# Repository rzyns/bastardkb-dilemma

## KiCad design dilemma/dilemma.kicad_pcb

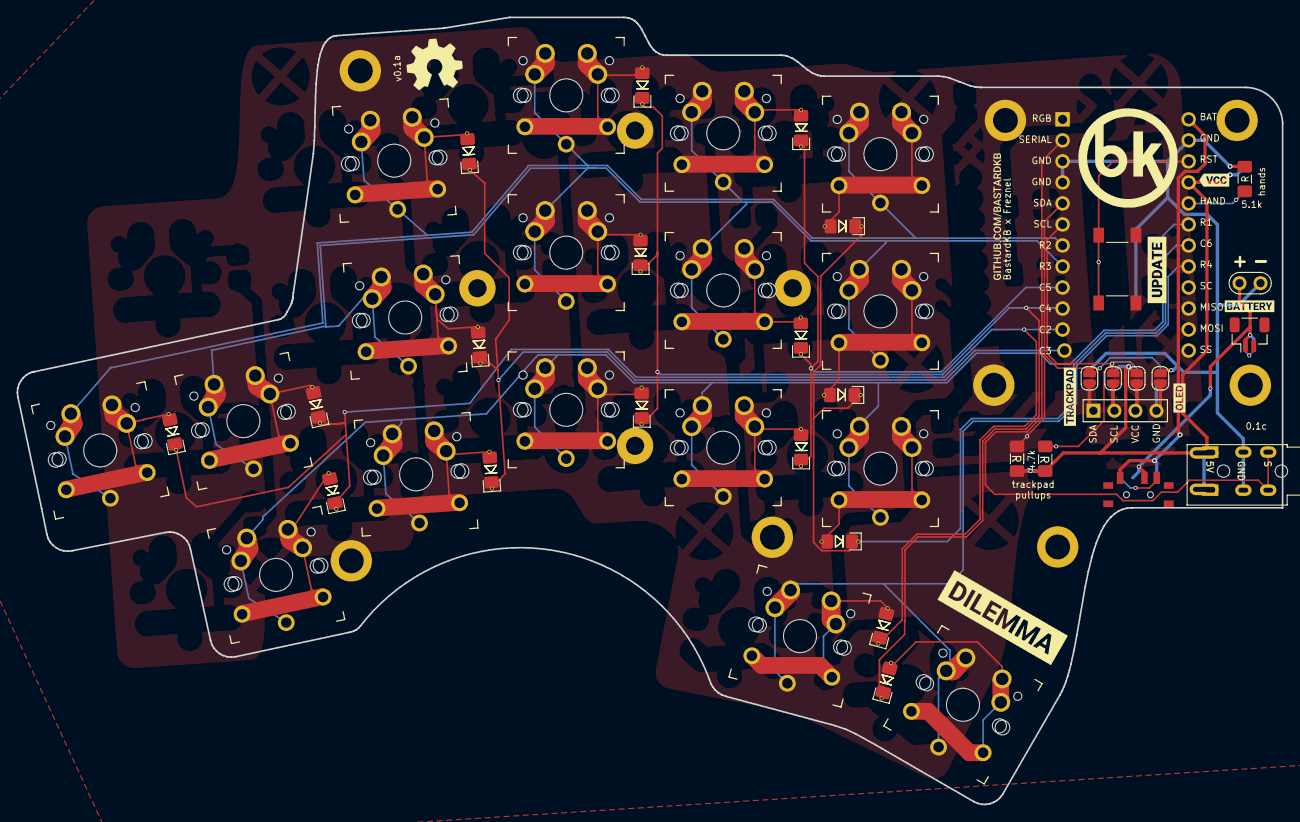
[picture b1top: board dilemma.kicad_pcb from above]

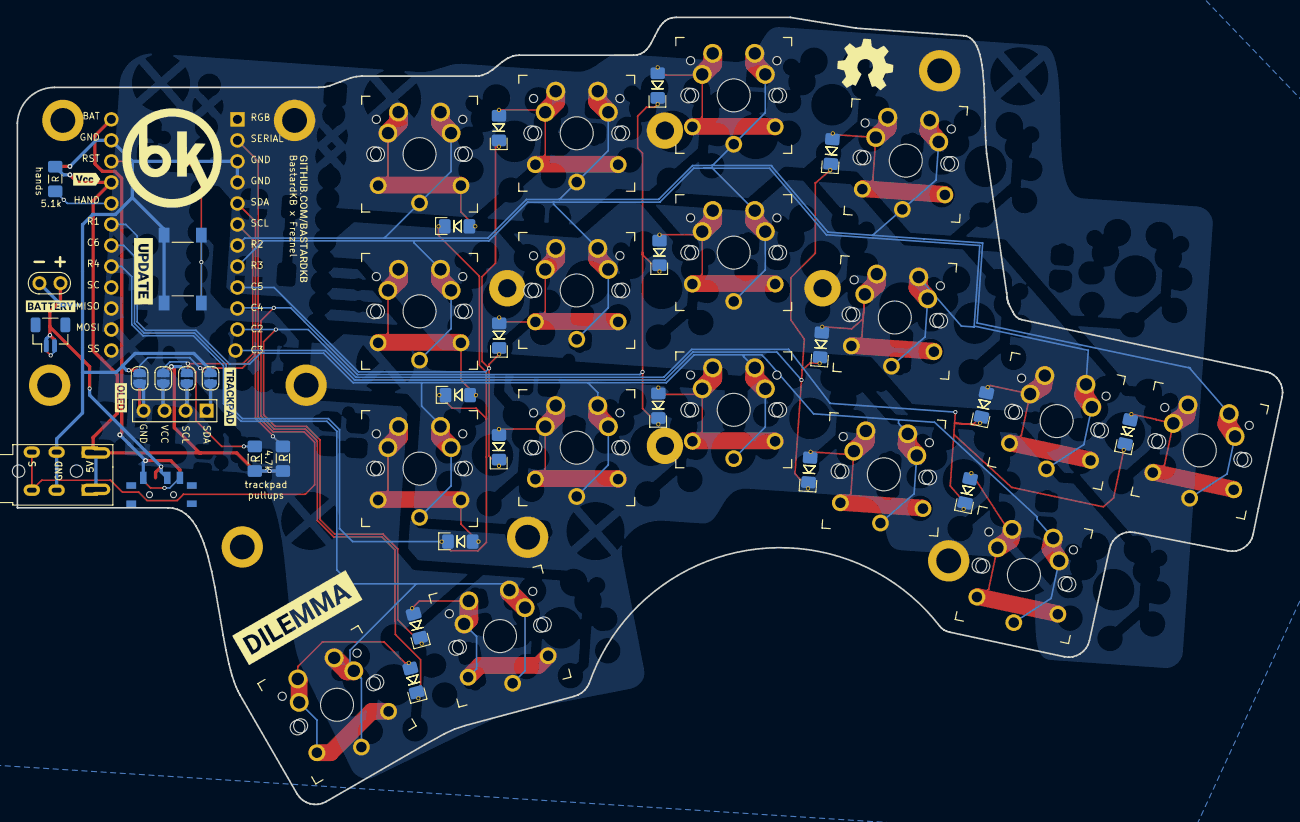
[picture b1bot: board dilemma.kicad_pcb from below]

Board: 2 copper layers, 152.9 x 95.1 mm, 77 parts (15 on the bottom side), 39 nets.

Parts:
D3, D4, D5, D8, D9, D10, D13, D14, D15, D18, D19, D20, D24, D25, D26, D30, D33: D; D_1206_handsolder_reversible
H1, H2, H4, H5, H6, H7, H8, H9: M4; MountingHole_3mm_Pad_thin
J1, J5: S3B-PH-SM4-TB(LF)(SN); JST_SH_BM02B-SRSS-TB_1x02-1MP_P1.00mm_Vertical
J2: Serial; Jack_3.5mm_PJ320E_Horizontal_reversible
J3: BATTERY_CONN_DEANS; battery_connector_THT
JP1, JP2, JP3, JP4, JP5, JP6, JP7, JP8: Jumper_2_Open; SolderJumper-2_P1.3mm_Open_RoundedPad1.0x1.5mm
O2: OLED; PinHeader_1x04_P2.54mm_Vertical
PSW1: SW_DPDT_x2; Switch_MSK-12C01-07
R1, R7: 5.1k; R_1206_handsolder
R3, R4: 4.7k; R_1206_handsolder_reversible
SW1, SW2, SW3, SW4, SW5, SW6, SW7, SW8, SW9, SW10, SW11, SW12, SW13, SW14, SW15, SW16: SW_Push; SW_MX_choc
SW17: locked; SW_MX_choc
SW26, SW37: SW_SPST; SW_Push_1P1T_NO_6x6mm_H9.5mm
U2: eliteC; pro-micro
kibuzzard-61F01A92, kibuzzard-61F01A92#2: G***; kibuzzard-61F01A92
kibuzzard-61F01C84, kibuzzard-61F01C84#2: G***; kibuzzard-61F01C84
kibuzzard-628D3AA1: G***; kibuzzard-628D3AA1
kibuzzard-628D396A: G***; kibuzzard-628D396A
kibuzzard-628DFB5F, kibuzzard-628DFB5F#2: G***; kibuzzard-628DFB5F
kibuzzard-628DFB48, kibuzzard-628DFB48#2: G***; kibuzzard-628DFB48
kibuzzard-628DFB95, kibuzzard-628DFB95#2: G***; kibuzzard-628DFB95
kibuzzard-628E0199, kibuzzard-628E0199#2: G***; kibuzzard-628E0199

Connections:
Gnd_l: H1.1, H2.1, H4.1, H5.1, H6.1, H7.1, H8.1, H9.1, J1.2, J2.R1, J3.-, J5.2, JP7.1 (A), JP8.1 (A), R1.2, SW26.2 (B), SW37.2 (B), U2.3 (GND), U2.4 (GND), U2.23 (GND)
unnamed: D3.2 (A), SW1.2
unnamed: D4.2 (A), SW2.2
unnamed: D5.2 (A), SW3.2
unnamed: D8.2 (A), SW4.2
unnamed: D9.2 (A), SW5.2
unnamed: D10.2 (A), SW6.2
unnamed: D13.2 (A), SW7.2
unnamed: D14.2 (A), SW8.2
unnamed: D15.2 (A), SW9.2
unnamed: D18.2 (A), SW10.2
unnamed: D19.2 (A), SW11.2
unnamed: D20.2 (A), SW12.2
unnamed: D24.2 (A), SW13.2
unnamed: D25.2 (A), SW14.2
unnamed: D26.2 (A), SW15.2
unnamed: D30.2 (A), SW16.2
unnamed: D33.2 (A), SW17.2
unnamed: JP1.2 (B), JP8.2 (B), O2.1
unnamed: JP2.2 (B), JP7.2 (B), O2.4
unnamed: JP3.2 (B), JP6.2 (B), O2.2
unnamed: JP4.2 (B), JP5.2 (B), O2.3
Rst_l: SW26.1 (A), SW37.1 (A), U2.22 (RST)
Vcc_l: J2.T, JP5.1 (A), JP6.1 (A), R3.2, R4.1, R7.2, U2.21 (VCC)
bat_l: PSW1.1 (A), U2.24 (RAW)
bat_sw_l: J1.1, J3.+, J5.1, PSW1.2 (B)
col1_l: D3.1 (K), D4.1 (K), D5.1 (K), D30.1 (K), U2.11 (B4)
col2_l: D8.1 (K), D9.1 (K), D10.1 (K), U2.12 (B5)
col3_l: D13.1 (K), D14.1 (K), D15.1 (K), D33.1 (K), U2.10 (E6)
col4_l: D18.1 (K), D19.1 (K), D20.1 (K), U2.9 (D7)
col5_l: D24.1 (K), D25.1 (K), D26.1 (K), U2.18 (F6)
hand: R1.1, R7.1, U2.20 (F4)
row1_l: SW16.1, SW17.1, U2.17 (F7)
row2_l: SW1.1, SW4.1, SW7.1, SW10.1, SW13.1, U2.7 (D4)
row3_l: SW2.1, SW5.1, SW8.1, SW11.1, SW14.1, U2.8 (C6)
row4_l: SW3.1, SW6.1, SW9.1, SW12.1, SW15.1, U2.19 (F5)
scl_l: JP3.1 (A), JP4.1 (A), R4.2, U2.6 (SDA)
sda_l: JP1.1 (A), JP2.1 (A), R3.1, U2.5 (SCL)
serial_l: J2.R2, U2.2 (RX)

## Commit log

2022-10-04 Add pinky clusters - first pass
